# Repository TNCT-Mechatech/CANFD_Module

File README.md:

# CANFD_Module
SPI->CAN FDに変換するモジュール

名前:ひなた
※画像は最新のものと比較すると古い部分があります．git pullして基板データを確認してください．
<br>

<br>

PCBAは[production/PCBA](production/PCBA)を参照してJLCPCBに発注してください．

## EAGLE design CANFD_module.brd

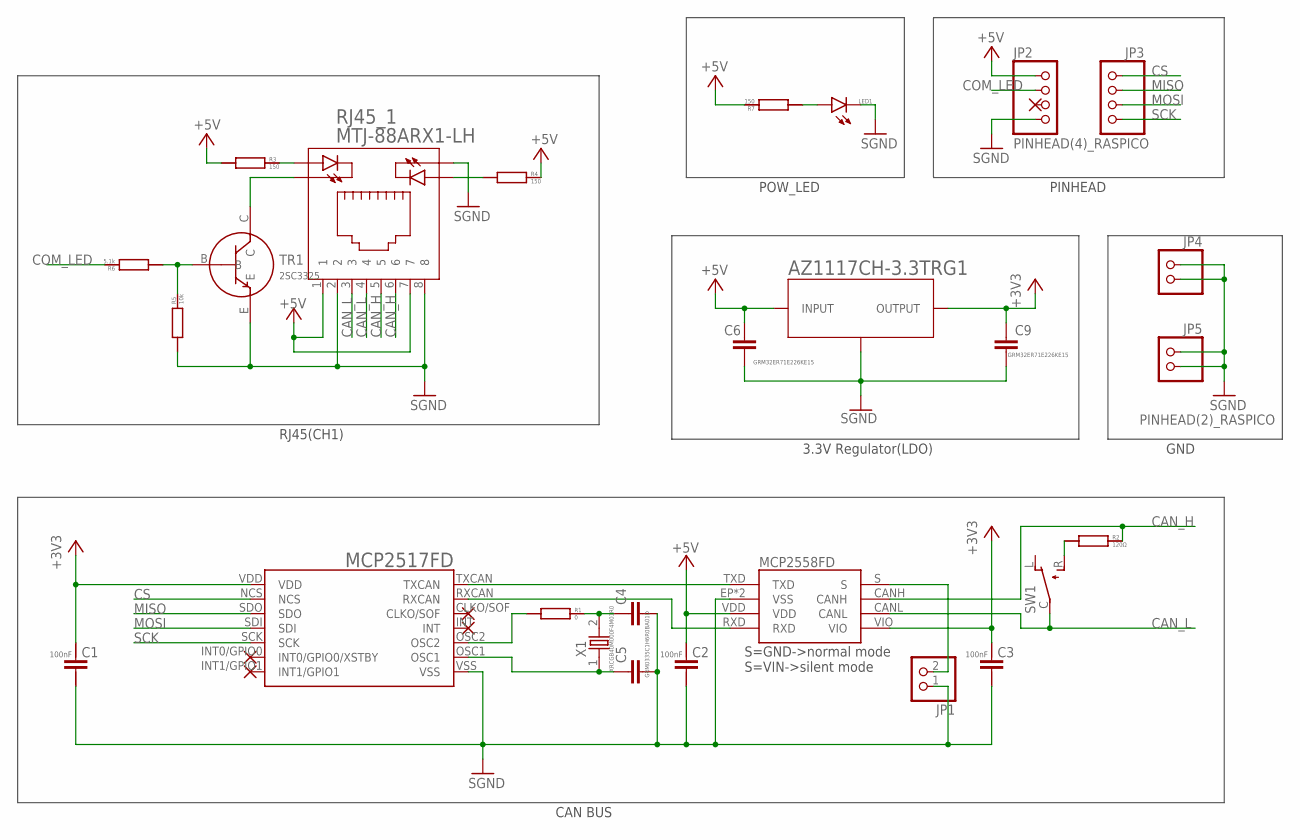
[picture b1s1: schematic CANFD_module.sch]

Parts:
C1, C2, C3: GCM188L81H104KA57
C4, C5: GRM0335C1H6R0BA01D; GRM0335C1H120GA01
C6, C9: GRM32ER71E226KE15; 3225M
JP1: PINHD-1X2; 1X02
JP2, JP3: PINHEAD(4)_RASPICO; 1X04
JP4, JP5: PINHEAD(2)_RASPICO; PINHEAD_2_RASPICO
LED1: SML-E12V8WT86
R1: 0; CR0603
R2: 120Ω; CR0603
R3, R4, R7: 150; CR0603
R5: 10k; CR0603
R6: 5.1k; CR0603
RJ45_1: MTJ-88ARX1-LH
SW1: SS-12SDP2
TR1: 2SC3325
U2: MCP2517FD
U$1: MCP2558FD
U$4: AZ1117CH-3.3TRG1; AZ1117C
X1: XRCGB40M000F4M01R0; XRCGB40M000F4M00R0

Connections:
+3V3: C1.P$1, C3.P$1, C9.L (1), U2.VDD, U$1.VIO, U$4.OUTPUT, U$4.VOUT (OUTPUT)
+5V: C2.P$1, C6.L (1), JP2.PIN1 (1), JP2.PIN1_ (1), R3.LEFT, R4.RIGHT, R7.RIGHT, RJ45_1.1, RJ45_1.7, U$1.VDD, U$4.INPUT
CAN_H: R2.RIGHT, RJ45_1.5, RJ45_1.6, U$1.CANH
CAN_L: RJ45_1.3, RJ45_1.4, SW1.C, U$1.CANL
COM_LED: JP2.PIN2 (2), JP2.PIN2_ (2), R6.RIGHT
CS: JP3.PIN1 (1), JP3.PIN1_ (1), U2.NCS
MISO: JP3.PIN2 (2), JP3.PIN2_ (2), U2.SDO
MOSI: JP3.PIN3 (3), JP3.PIN3_ (3), U2.SDI
unnamed: LED1.A, R7.LEFT
unnamed: R2.LEFT, SW1.R
unnamed: U2.TXCAN, U$1.TXD
unnamed: U2.RXCAN, U$1.RXD
unnamed: R1.LEFT, U2.OSC2
unnamed: C5.1, U2.OSC1, X1.1
unnamed: C4.1, R1.RIGHT, X1.2
unnamed: R4.LEFT, RJ45_1.LED2_A
unnamed: JP1.2, U$1.S
unnamed: R3.RIGHT, RJ45_1.LED1_A
unnamed: RJ45_1.LED1_K, TR1.C
unnamed: R5.RIGHT, R6.LEFT, TR1.B
SCK: JP3.PIN4 (4), JP3.PIN4_ (4), U2.SCK
SGND: C1.P$2, C2.P$2, C3.P$2, C4.2, C5.2, C6.R (2), C9.R (2), JP1.1, JP2.PIN4 (4), JP2.PIN4_ (4), JP4.PIN1 (1), JP4.PIN1_ (1), JP4.PIN2 (2), JP4.PIN2_ (2), JP5.PIN1 (1), JP5.PIN1_ (1), JP5.PIN2 (2), JP5.PIN2_ (2), LED1.K (C), R5.LEFT, RJ45_1.2, RJ45_1.8, RJ45_1.LED2_K, TR1.E, U2.VSS, U$1.EP (VSS), U$1.VSS, U$4.GND

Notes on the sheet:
S=GND->normal mode S=VIN->silent mode
CAN BUS
RJ45(CH1)
3.3V Regulator(LDO)
PINHEAD
POW_LED
GND

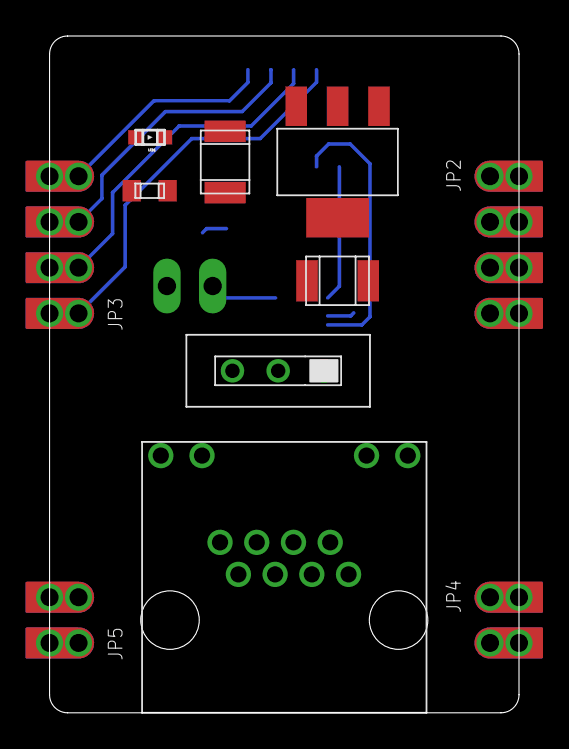
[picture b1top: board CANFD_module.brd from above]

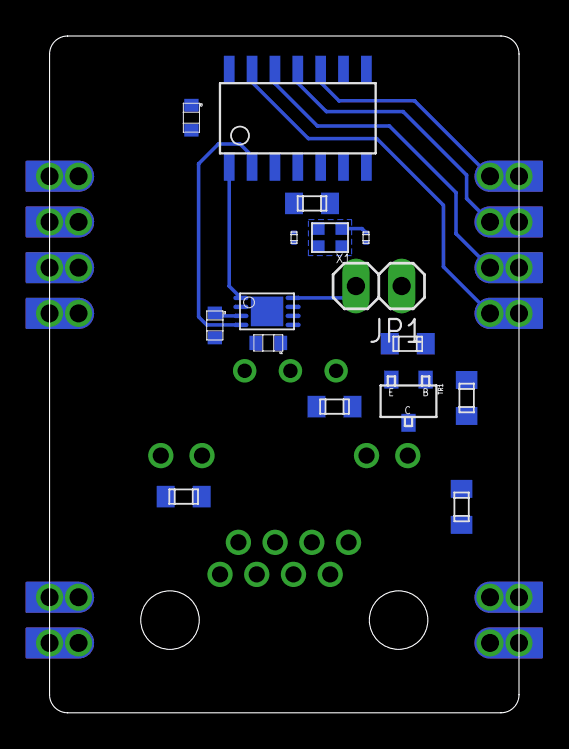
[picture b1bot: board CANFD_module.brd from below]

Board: 2 copper layers, 26.1 x 37.6 mm, 27 parts (16 on the bottom side), 22 nets.

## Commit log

2023-03-29 途中まで
2023-03-29 Create license
2023-03-30 基板完成
2023-03-30 基板微修正
2023-10-22 [fix]0603->1608 package
2023-11-03 [fix]ピンアサインをver1.0と同じにした
2023-11-03 [fix]versionの表示
2023-11-15 [add]PCBA用のBOMを追加
2023-11-15 rm ignore files
2023-11-15 rm gerber files
